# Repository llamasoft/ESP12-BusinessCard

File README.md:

# ESP-12 PCB Business Card

This is my personal take on a PCB business card build around the ESP-12/ESP8266 WiFi SoC.  
The board was designed using [AutoDesk Eagle](https://www.autodesk.com/products/eagle/free-download) and fabricated/assembled by [JLCPCB](https://jlcpcb.com/).

## Personalizing

Load up the Eagle .brd file, then replace the dummy information with your actual information.  Export the Gerber files for your PCB manufacturer and you're good to go!

**NOTE:** The text will need to be updated on the "bottom" (layer 16) and "bStop" (layer 30) layers.  This is what allows the text's copper to be exposed.  Without modifying the "bStop" layer, your text will be hidden under the solder mask layer.  

**WARNING:** The provided `assembly.csv` file assumes that you didn't modify the location of any components.  If you did, you will need to manually recreate it.

***EXTRA WARNING:*** JLCPCB's fabrication library has the AMS1117 voltage regulator rotated differently than Eagle's libraries.  If you recreate it, you will need to manually modify the `assembly.csv` file to correct this.  Please be sure to use your manufacturer's "board preview" tools to verify the positioning of all board components.

## Assembly

All board SMD components are standard off-the-shelf parts.  Your PCB manufacturer should be able to supply most of them for you.  Larger size components have been selected to make hand-assembly easier.  All passive components use a 0805 footprint with the exception of the optional power LED (0603).

The only components you will likely need to purchase separately are the ESP-12 and micro-USB header:

- For the ESP-12, I personally recommend this [AliExpress listing](https://www.aliexpress.com/item/4000232588723.html).  At the time of writing, each chip comes out to $1.29 each, shipped.  If you have the option to get the ESP-12F over the ESP-12E as it has an optimized antenna.  
- For the micro-USB header: good luck.  They come in so many different footprints that it will be difficult to select the correct one.  For that reason, the PCB also has the USB lines broken out into standard 2.54mm headers.  This allows you to use a regular micro-USB breakout board instead, which should be much easier to acquire and solder.

## Example Images

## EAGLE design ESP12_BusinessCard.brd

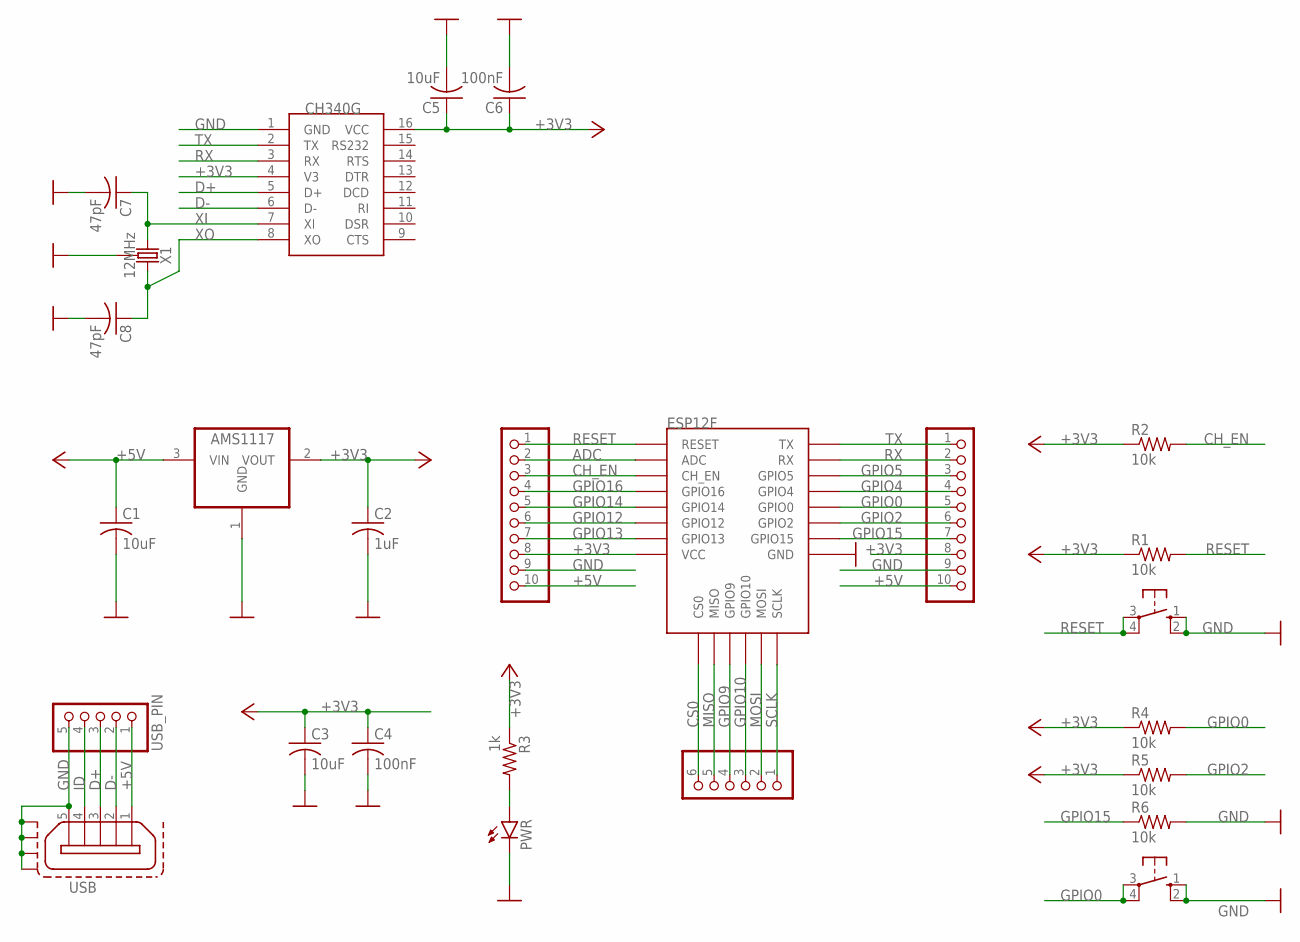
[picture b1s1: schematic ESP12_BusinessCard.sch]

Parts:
AMS1117: AMS1117; SOT223; LCSC C6186
C1, C3, C5: 10uF; C0805; LCSC C15850
C2: 1uF; C0805; LCSC C28323
C4, C6: 100nF; C0805; LCSC C49678
C7, C8: 47pF; C0805; LCSC C14857
CH340G: CH340G; SOIC16; LCSC C14267
ESP12F: ESP12FSMD; ESP12E-SMD
JP1, JP2: PINHD-1X10; 1X10
JP3: PINHD-1X6; 1X06
PWR: LEDCHIP-LED0603; CHIP-LED0603; LCSC C2286
R1, R2, R4, R5, R6: 10k; R0805; LCSC C17414
R3: 1k; R0805; LCSC C17513
S_PROG: 10-XX; B3F-10XX
S_RESET: 10-XX; B3F-10XX
USB: ZX62D-B-5PA8
USB_PIN: PINHD-1X5; 1X05
X1: 12MHz; CRYSTAL-SMD-3.2X2.5MM; LCSC C9002

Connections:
+3V3: AMS1117.2 (VOUT), C2.1, C3.1, C4.1, C5.1, C6.1, CH340G.4 (V3), CH340G.16 (VCC), ESP12F.VCC, JP1.8, JP2.8, R1.1, R2.1, R3.1, R4.1, R5.1
+5V: AMS1117.3 (VIN), C1.1, JP1.10, JP2.10, USB.1, USB_PIN.1
ADC: ESP12F.ADC, JP1.2
CH_EN: ESP12F.CH_PD (CH_EN), JP1.3, R2.2
CS0: ESP12F.CS0, JP3.6
D+: CH340G.5 (D+), USB.3, USB_PIN.3
D-: CH340G.6 (D-), USB.2, USB_PIN.2
GND: AMS1117.1 (GND), C1.2, C2.2, C3.2, C4.2, C5.2, C6.2, C7.2, C8.2, CH340G.1 (GND), ESP12F.GND, JP1.9, JP2.9, PWR.C, R6.2, S_PROG.1 (S), S_PROG.2 (S1), S_RESET.1 (S), S_RESET.2 (S1), USB.5, USB.S1, USB.S2, USB.S3, USB.S4, USB_PIN.5, X1.2 (3), X1.4 (3)
GPIO0: ESP12F.GPIO0, JP2.5, R4.2, S_PROG.3, S_PROG.4 (P1)
GPIO2: ESP12F.GPIO2, JP2.6, R5.2
GPIO4: ESP12F.GPIO4, JP2.4
GPIO5: ESP12F.GPIO5, JP2.3
GPIO9: ESP12F.GPIO9, JP3.4
GPIO10: ESP12F.GPIO10, JP3.3
GPIO12: ESP12F.GPIO12, JP1.6
GPIO13: ESP12F.GPIO13, JP1.7
GPIO14: ESP12F.GPIO14, JP1.5
GPIO15: ESP12F.GPIO15, JP2.7, R6.1
GPIO16: ESP12F.GPIO16, JP1.4
ID: USB.4, USB_PIN.4
MISO: ESP12F.MISO, JP3.5
MOSI: ESP12F.MOSI, JP3.2
unnamed: PWR.A, R3.2
RESET: ESP12F.RESET, JP1.1, R1.2, S_RESET.3, S_RESET.4 (P1)
RX: CH340G.3 (RX), ESP12F.RXD0 (RX), JP2.2
SCLK: ESP12F.SCLK, JP3.1
TX: CH340G.2 (TX), ESP12F.TXD0 (TX), JP2.1
XI: C7.1, CH340G.7 (XI), X1.1
XO: C8.1, CH340G.8 (XO), X1.3 (2)

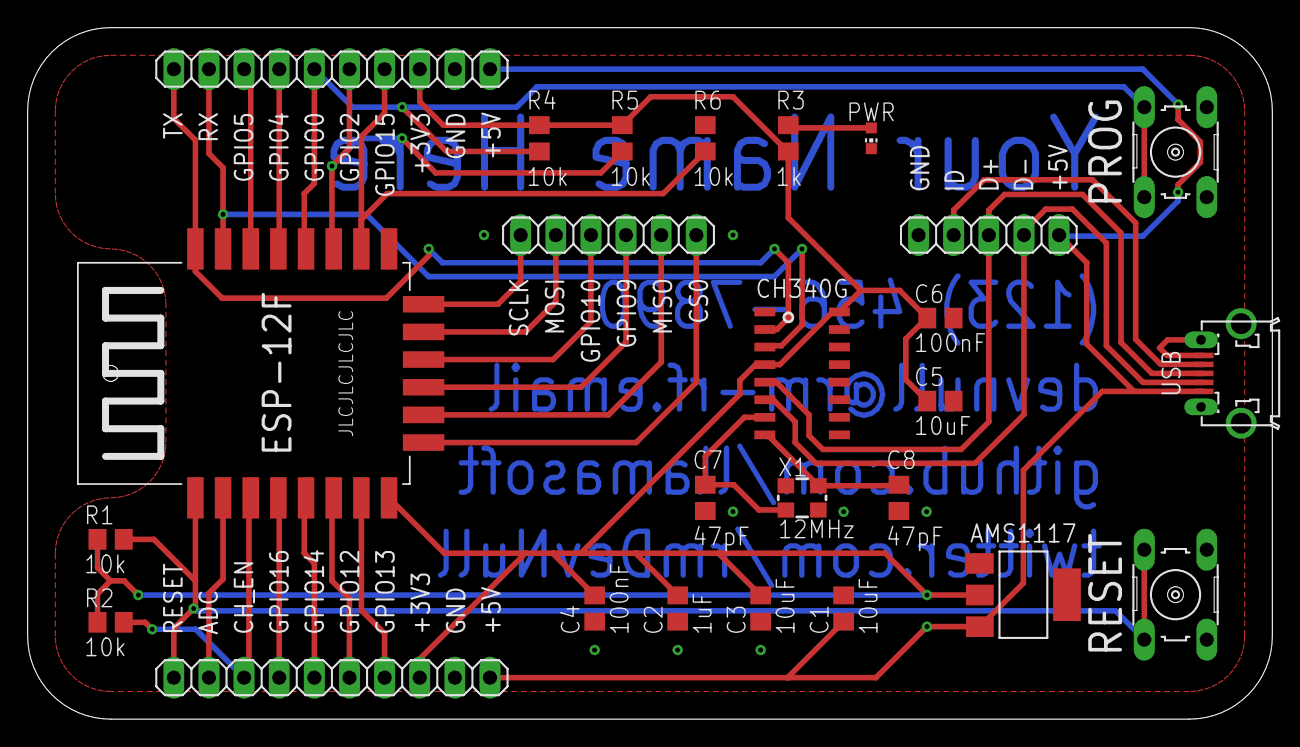
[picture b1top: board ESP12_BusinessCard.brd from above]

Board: 2 copper layers, 90.0 x 50.0 mm, 26 parts (0 on the bottom side), 29 nets.

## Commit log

2020-03-28 Initial empty commit
2020-03-28 Add PCB files
2020-03-31 Add PCB images
2020-03-31 Add README.md
